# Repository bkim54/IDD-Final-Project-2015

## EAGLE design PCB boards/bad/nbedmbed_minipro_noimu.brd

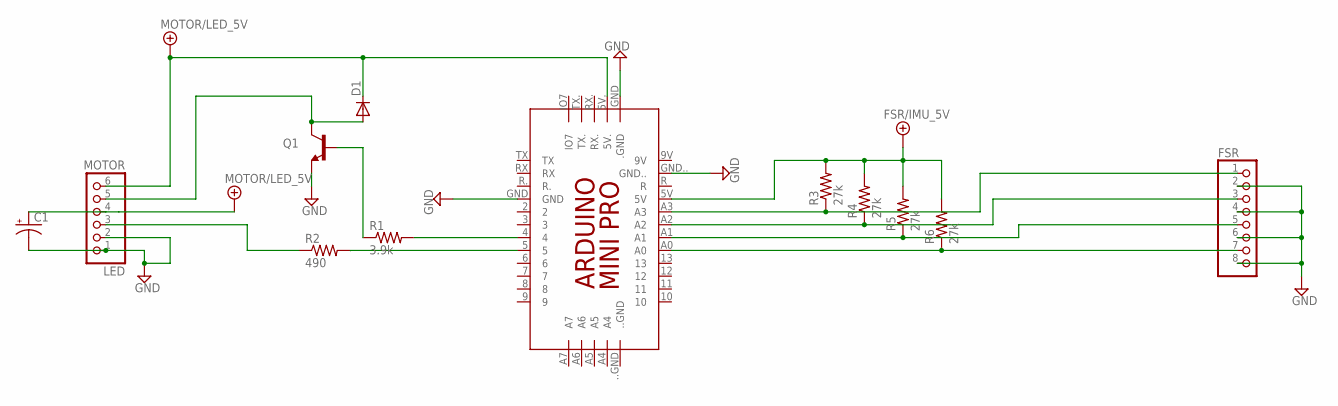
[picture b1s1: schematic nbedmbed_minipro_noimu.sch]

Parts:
C1: CAP_POLPTH1; CPOL-RADIAL-100UF-25V
D1: DIODE1N4148; DIODE-1N4148
FSR: PINHD-1X8BIG; 1X08-BIG
LED: MOTOR; 1X06-BIG
PCB2: ARDUINO_MINI_PRO
Q1: TRANSISTOR_NPNTO-92-AMMO; TO-92-AMMO
R1: 3.9k; 1/6W-RES
R2: 490; 1/6W-RES
R3, R4, R5, R6: 27k; 1/6W-RES

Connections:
FSR/IMU_5V: PCB2.5V, R3.2, R4.2, R5.2, R6.2
GND: C1.2 (-), FSR.2, FSR.4, FSR.6, FSR.8, LED.1, LED.2, PCB2..GND, PCB2.GND, PCB2.GND.., Q1.1 (E)
MOTOR/LED_5V: C1.1 (+), D1.C, LED.4, LED.6, PCB2.5V.
unnamed: PCB2.4, R1.2
unnamed: PCB2.5, R2.2
unnamed: Q1.2 (B), R1.1
unnamed: LED.3, R2.1
unnamed: FSR.1, PCB2.A3, R3.1
unnamed: FSR.3, PCB2.A2, R4.1
unnamed: D1.A, LED.5, Q1.3 (C)
unnamed: FSR.5, PCB2.A1, R5.1
unnamed: FSR.7, PCB2.A0, R6.1

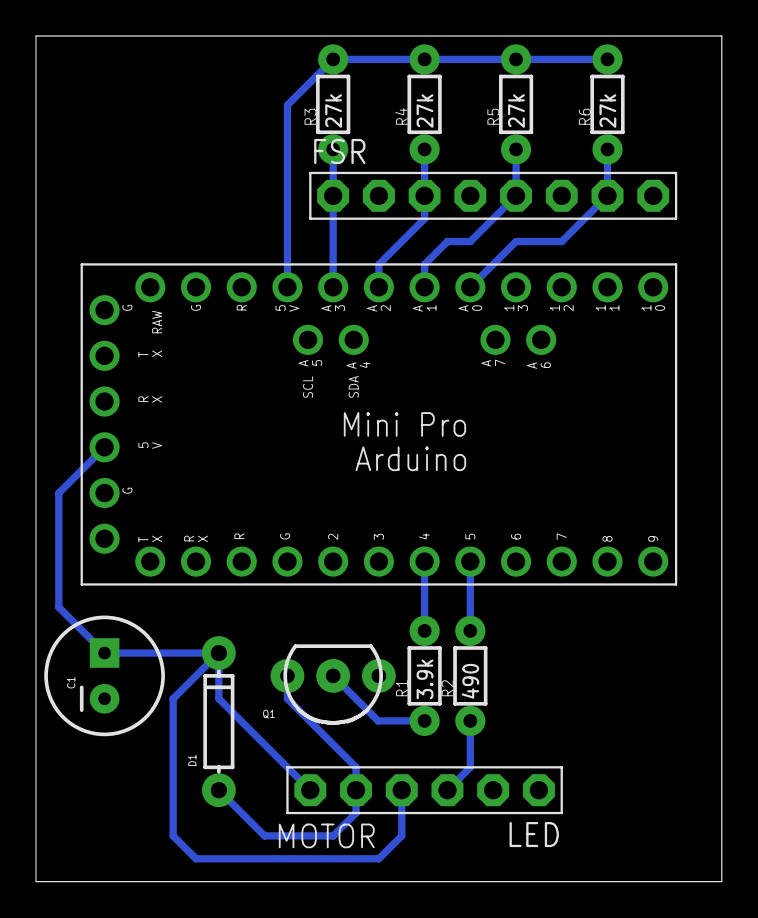
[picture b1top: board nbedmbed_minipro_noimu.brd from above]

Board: 2 copper layers, 38.1 x 47.0 mm, 12 parts (0 on the bottom side), 12 nets.

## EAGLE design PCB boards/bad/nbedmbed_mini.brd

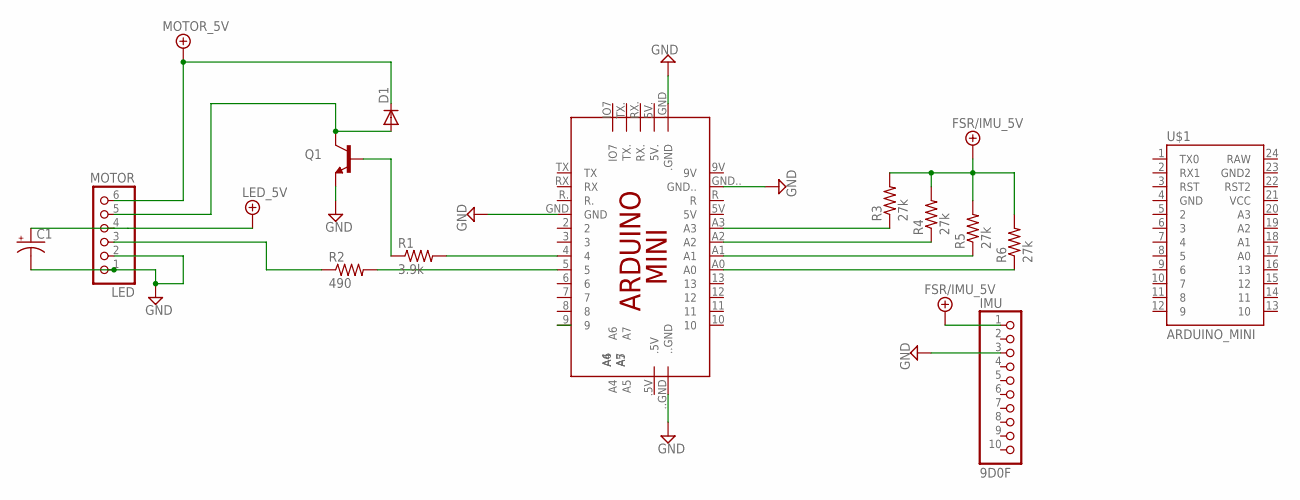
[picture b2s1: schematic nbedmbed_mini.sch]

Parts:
C1: CAP_POLPTH1; CPOL-RADIAL-100UF-25V
D1: DIODE1N4148; DIODE-1N4148
IMU: 9D0F; 1X10-BIG
LED: MOTOR; 1X06-BIG
PCB1: ARDUINO_MINI
Q1: TRANSISTOR_NPNTO-92-AMMO; TO-92-AMMO
R1: 3.9k; 1/6W-RES
R2: 490; 1/6W-RES
R3, R4, R5, R6: 27k; 1/6W-RES
U$1: ARDUINO_MINI

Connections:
FSR/IMU_5V: IMU.1, R3.2, R4.2, R5.2, R6.2
GND: C1.2 (-), IMU.3, LED.1, LED.2, PCB1...GND, PCB1..GND, PCB1.GND, PCB1.GND.., Q1.1 (E)
LED_5V: C1.1 (+), LED.4
MOTOR_5V: D1.C, LED.6
unnamed: PCB1.4, R1.2
unnamed: Q1.2 (B), R1.1
unnamed: LED.3, R2.1
unnamed: PCB1.A0, R6.1
unnamed: PCB1.5, R2.2
unnamed: D1.A, LED.5, Q1.3 (C)
unnamed: PCB1.A1, R5.1
unnamed: PCB1.A2, R4.1
unnamed: PCB1.A3, R3.1

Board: 2 copper layers, 13 parts (0 on the bottom side), 13 nets, no tracks yet.

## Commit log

2015-11-02 added basic python REST server code
2015-11-03 adding arduino code
2015-11-04 changed arduino code to output correctly formatted strings. Also in python program parsed the strings read in from USB serial and took a moving average to determine if pivoting from wirst or elbow
2015-11-05 website UI now looks somewhat complete. Will fill in graphs next
2015-11-09 put in disconnection
2015-11-09 stuff
2015-11-09 moved css stuff into static folder
2015-11-09 removed folders
2015-11-09 testing getting a dict
2015-11-09 fixed server code
2015-11-10 realtime graph updates
2015-11-10 added FSR database and added server GET methods
2015-11-12 added fake generator, modified server
2015-11-12 javacsript doesn't work but i need to leave
2015-11-16 added LED and motor to arduino code
2015-11-16 changed a buncha shit
2015-11-29 updated arduino code
2015-11-30 added mouse display
2015-11-30 uncommented the js for the other parts
2015-11-30 changed scaling of FSR reading
2015-11-30 added console log
2015-11-30 shit
2015-11-30 message
2015-11-30 more shit
2015-12-08 revamped the website for no good reason
2015-12-08 minor summary addition
2015-12-09 added server stuff
2015-12-09 added force table shit
2015-12-10 i hate life
2015-12-10 changed update on arudino
2015-12-10 need to chnage FSR values to floats

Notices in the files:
parts and their libraries:
SparkFun-DiscreteSemi: Licensing: CC v3.0 Share-Alike You are welcome to use this library for commercial purposes.
